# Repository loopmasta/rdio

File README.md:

# rdio

**rdio** turns your iPhone into a VHF/UHF radio. It connects to one or more ESP32-powered devices equipped with radio modules over Wi-Fi. Listen to transmissions, talk with push-to-talk, save your favourite channels and repeaters, and exchange APRS messages in a familiar chat-style interface.

**[Get the app on the App Store](https://apps.apple.com/de/app/rdio/id6831735571?l=en-GB)**

<table>
  <tr>
    <td align="center"></td>
    <td align="center"></td>
    <td align="center"></td>
    <td align="center"></td>
    <td align="center"></td>
  </tr>
  <tr>
    <td align="center">Main screen</td>
    <td align="center">Transmit</td>
    <td align="center">APRS chat</td>
    <td align="center">Channel editor</td>
    <td align="center">Settings</td>
  </tr>
</table>

## How it works

- The ESP32 opens its own Wi-Fi network (or joins one you configure). The phone connects to it and talks to the radio over a WebSocket. Radios on a shared network are found automatically (Bonjour), so one app can control several of them.
- Receive audio goes from the radio to the phone as 16 kHz mono PCM. Transmit audio goes the other way while you hold the push-to-talk button.
- The module is tuned, squelched and keyed by the ESP32 through its UART, PTT and power-down lines.
- Bluetooth is not used.

## Features

- **Receive and transmit** in the selected band (VHF 134–174 MHz or UHF 400–480 MHz).
- **Channel list** with simplex and duplex (repeater) entries, shift direction and offset, CTCSS transmit and receive tones, and a 1750 Hz tone burst. Reorder by dragging, swipe to edit or delete.
- **APRS** on 1200 baud AFSK: the app decodes received packets (positions, Mic-E, messages, status) on APRS channels, shows them as a chat with distance and a link to Maps, links call signs to QRZ.com. You can also send: type a message in the chat to a call sign or to CQ. Messages to a station are repeated until it acknowledges them, the app acknowledges messages addressed to you, and everything is sent only while the channel is clear. A periodic position beacon is available too.
- **Several radios:** each radio announces itself on the network as a Bonjour service (`_rdio._tcp`, with its name, module type and firmware version). The app lists the radios it finds in Settings → Radio and switches between them with one tap. Give every radio its own name (Settings → Radio Name), because the name is also its Wi-Fi and host name.
- **Phone microphone chain** with a compressor and a mic level setting, soft limiter on the radio side.
- **Native iOS design**: system controls, Light and Dark Mode, Dynamic Type, VoiceOver, haptics, no navigation bar.
- **Transmit safety**: the app only transmits inside the selected band, and the firmware releases the push-to-talk line when the connection drops, when no audio arrives, and after 120 seconds. Only one client can transmit.
- **Transmit power:** high (1 W) or low (0.5 W) with a switch in Settings → Radio. The radio remembers the choice; low power draws about half as much from the battery while transmitting.
- Firmware updates over Wi-Fi.

## Status

Working on a real radio: receive, transmit, channel handling, tones, tone burst, APRS decoding, and the APRS position beacon (tested over the air).

Not done yet: a scan function in the app.

The carrier board is built and works: receive, transmit, the transmit audio level and the power switch were tested on the air. The harmonic filters below are **designed but not built or measured yet**. They are simulated only; check them with a NanoVNA before relying on them.

## Hardware

Everything is KiCad 10 and is generated by scripts, so the boards can be rebuilt and changed in code.

### Carrier board

A 57.3 × 25.4 mm two-layer board for an ESP32 38-pin DevKit (NodeMCU-32S style) and a DRA818 / SA818 module. The DevKit's own pins are soldered into the board from below, the radio module sits on the top side, and an SMA jack on the end opposite the DevKit's USB port carries the antenna signal on a short track.

<table>
  <tr>
    <td align="center"></td>
    <td align="center"></td>
  </tr>
  <tr>
    <td align="center">Top: radio module, DevKit below, SMA jack</td>
    <td align="center">Bottom: audio and supply parts, DevKit pin rows</td>
  </tr>
</table>

| Function | ESP32 pin |
|---|---|
| Module UART (RX / TX) | GPIO16 / GPIO17 |
| Power down (high = on) | GPIO19 |
| PTT (low = transmit) | GPIO18 |
| Squelch in | GPIO32 |
| RX audio in (ADC) | GPIO34, biased to 1.75 V by GPIO26 |
| TX audio out | GPIO25 |
| High / low power | GPIO23 (the firmware pulls it low for 0.5 W and leaves it floating for 1 W; it never drives it high) |

- The module's supply pin is fed straight from the DevKit's 5 V pin, with a 47 µF and a 100 nF capacitor next to the module. The module's datasheet allows 3.3 to 4.5 V, so check the voltage on your DevKit's 5 V pin (many boards drop it through a diode from USB) before the first power-up.
- Pin numbers, the module name and the antenna end are printed on the top silkscreen inside the module outline, to help with placing it.
- Test status: built and working. The module's footprint and the DevKit's pin spacing were checked against real parts. The transmit network (22 k in series, 220 Ω and 220 nF to ground) divides the signal by about 100 and rolls it off from a few hundred hertz, so the firmware compensates with a higher transmit gain and a first-order treble boost (`firmware/idf/main/board.h`); the level and the frequency response were checked through a second radio.

### Harmonic filters (2 m and 70 cm)

Two small all-SMD low-pass filters (7th-order Chebyshev, 0.1 dB ripple, 50 Ω) that go between the board's SMA jack and the antenna and cut the radio module's harmonics. Details, simulation and parts notes: [hardware/filter/README.md](hardware/filter/README.md).

<table>
  <tr>
    <td align="center"></td>
    <td align="center"></td>
  </tr>
  <tr>
    <td align="center">2 m, 144–146 MHz</td>
    <td align="center">70 cm, 430–440 MHz</td>
  </tr>
</table>

| | 2 m | 70 cm |
|---|---|---|
| Passband | 144–146 MHz | 430–440 MHz |
| Insertion loss (simulated) | 0.56 dB | 0.50 dB |
| 2nd harmonic (simulated) | 52 dB down | 63 dB down |
| Board size | 38.0 × 12.4 mm | 34.4 × 12.4 mm |

### Ordering the boards

Gerber, drill, bill of materials and placement files for JLCPCB are in [hardware/jlcpcb/](hardware/jlcpcb/): `radio/` for the carrier board and `filters/vhf`, `filters/uhf` for the filters. Check the LCSC part numbers in the bills of materials against JLCPCB's parts library before you order. The SMA connectors, the DevKit headers and the radio module are soldered by hand.

## Legal

Transmitting needs an amateur radio licence and must follow the rules that apply to you. The app limits the transmit frequency to the selected band, but you are responsible for staying within your licence and the local regulations.

**Privacy:** the app has no accounts, analytics or tracking. See the [privacy policy](https://loopmasta.github.io/rdio/privacy/).

## Repository contents

This repository lets a small group of testers order the hardware, build it, flash the firmware and install the app, with no software knowledge or development tools. It holds the hardware design (`hardware/`), the screenshots (`docs/`) and this description.

The software is not included and does not need to be built:

- **iOS app:** [download rdio from the App Store](https://apps.apple.com/de/app/rdio/id6831735571?l=en-GB).
- **Firmware:** installed from your browser with the [web flasher](https://loopmasta.github.io/rdio/flash/). Connect the ESP32 over USB, open the page in Chrome or Edge on a computer and press install.

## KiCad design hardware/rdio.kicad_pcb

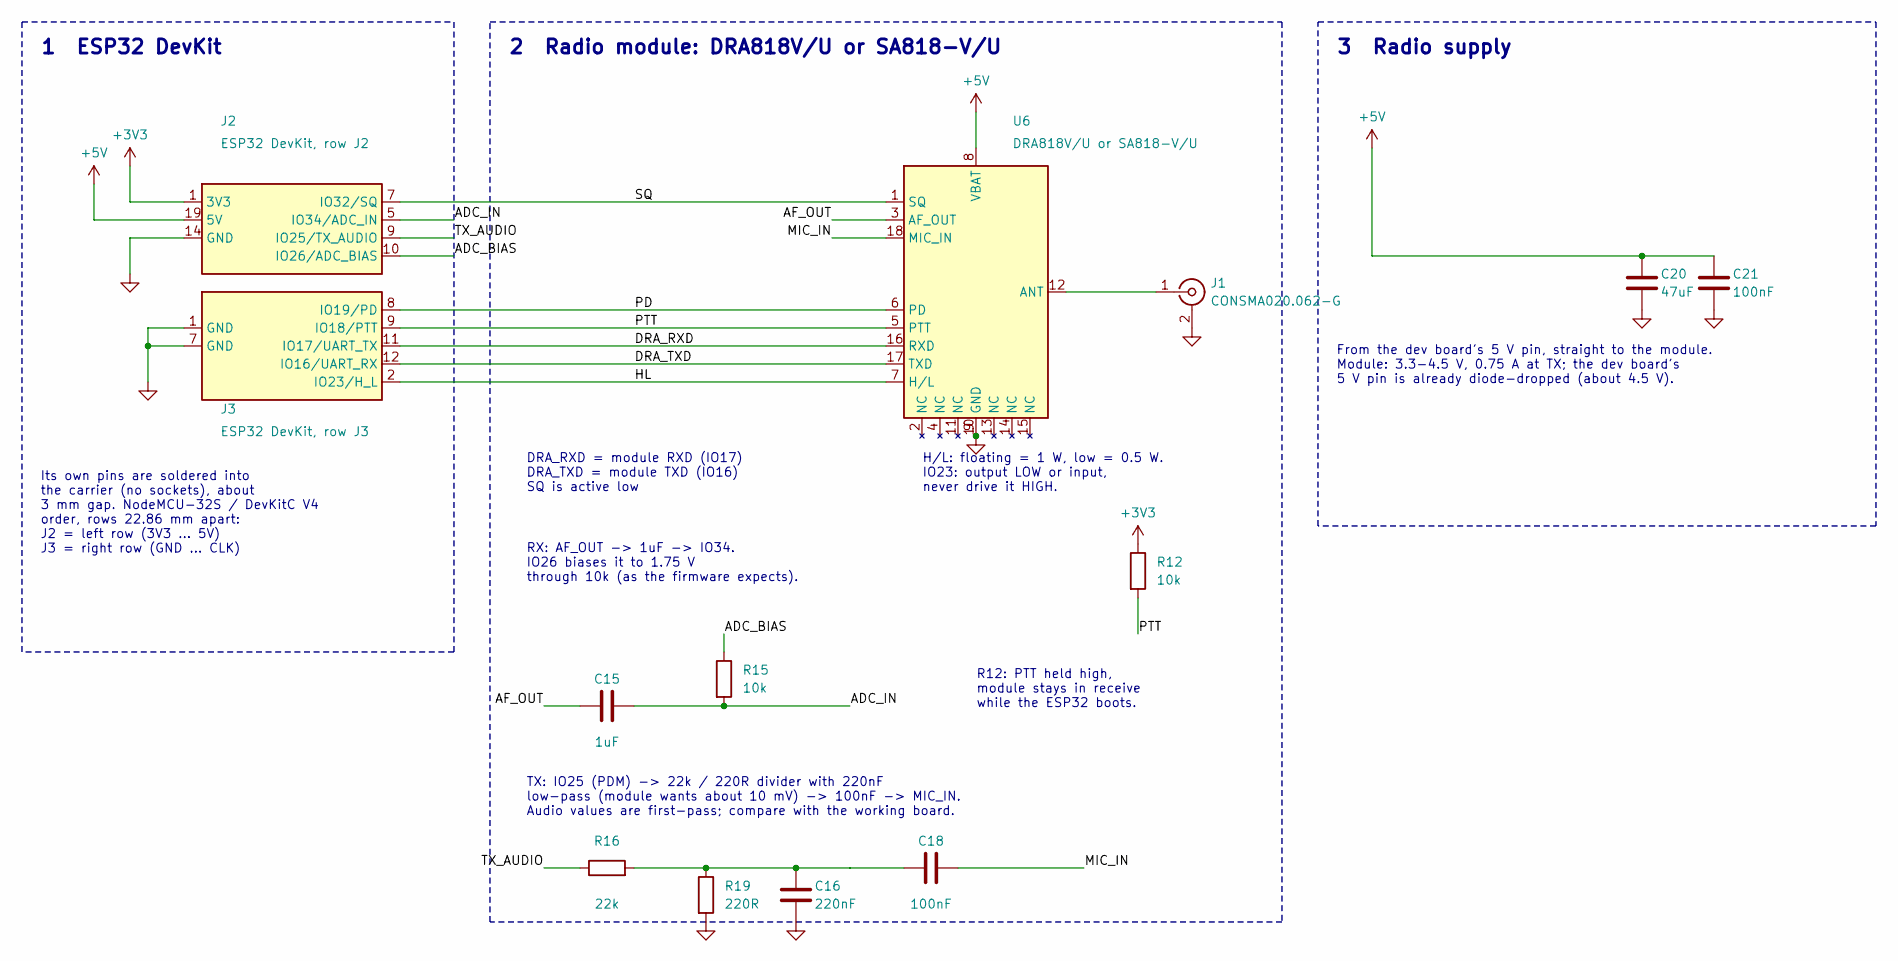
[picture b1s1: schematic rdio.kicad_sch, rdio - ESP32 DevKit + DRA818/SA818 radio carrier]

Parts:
C15: 1uF; C_0603_1608Metric
C16: 220nF; C_0603_1608Metric
C18, C21: 100nF; C_0603_1608Metric
C20: 47uF; C_1206_3216Metric
J1: CONSMA020.062-G; CONSMA020_062_G
J2: ESP32 DevKit, row J2; PinHoles_1x19_P2.54mm
J3: ESP32 DevKit, row J3; PinHoles_1x19_P2.54mm
R12, R15: 10k; R_0603_1608Metric
R16: 22k; R_0603_1608Metric
R19: 220R; R_0603_1608Metric
U6: DRA818V/U or SA818-V/U; DRA818_SA818

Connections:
+3V3: J2.1 (3V3), R12.1
+5V: C20.1, C21.1, J2.19 (5V), U6.8 (VBAT)
/ADC_BIAS: J2.10 (IO26/ADC_BIAS), R15.1
/ADC_IN: C15.2, J2.5 (IO34/ADC_IN), R15.2
/AF_OUT: C15.1, U6.3 (AF_OUT)
/DRA_RXD: J3.11 (IO17/UART_TX), U6.16 (RXD)
/DRA_TXD: J3.12 (IO16/UART_RX), U6.17 (TXD)
/HL: J3.2 (IO23/H_L), U6.7 (H/L)
/MIC_IN: C18.2, U6.18 (MIC_IN)
/PD: J3.8 (IO19/PD), U6.6 (PD)
/PTT: J3.9 (IO18/PTT), R12.2, U6.5 (PTT)
/SQ: J2.7 (IO32/SQ), U6.1 (SQ)
/TX_AUDIO: J2.9 (IO25/TX_AUDIO), R16.1
GND: C16.2, C20.2, C21.2, J1.2 (Ext), J2.14 (GND), J3.1 (GND), J3.7 (GND), R19.2, U6.9 (GND), U6.10 (GND)
unnamed: C16.1, C18.1, R16.2, R19.1
unnamed: J1.1 (In), U6.12 (ANT)

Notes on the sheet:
1 ESP32 DevKit
Its own pins are soldered into the carrier (no sockets), about 3 mm gap. NodeMCU-32S / DevKitC V4 order, rows 22.86 mm apart: J2 = left row (3V3 ... 5V) J3 = right row (GND ... CLK)
2 Radio module: DRA818V/U or SA818-V/U
DRA_RXD = module RXD (IO17) DRA_TXD = module TXD (IO16) SQ is active low
H/L: floating = 1 W, low = 0.5 W. IO23: output LOW or input, never drive it HIGH.
R12: PTT held high, module stays in receive while the ESP32 boots.
RX: AF_OUT -> 1uF -> IO34. IO26 biases it to 1.75 V through 10k (as the firmware expects).
TX: IO25 (PDM) -> 22k / 220R divider with 220nF low-pass (module wants about 10 mV) -> 100nF -> MIC_IN. Audio values are first-pass; compare with the working board.
3 Radio supply
From the dev board's 5 V pin, straight to the module. Module: 3.3-4.5 V, 0.75 A at TX; the dev board's 5 V pin is already diode-dropped (about 4.5 V).

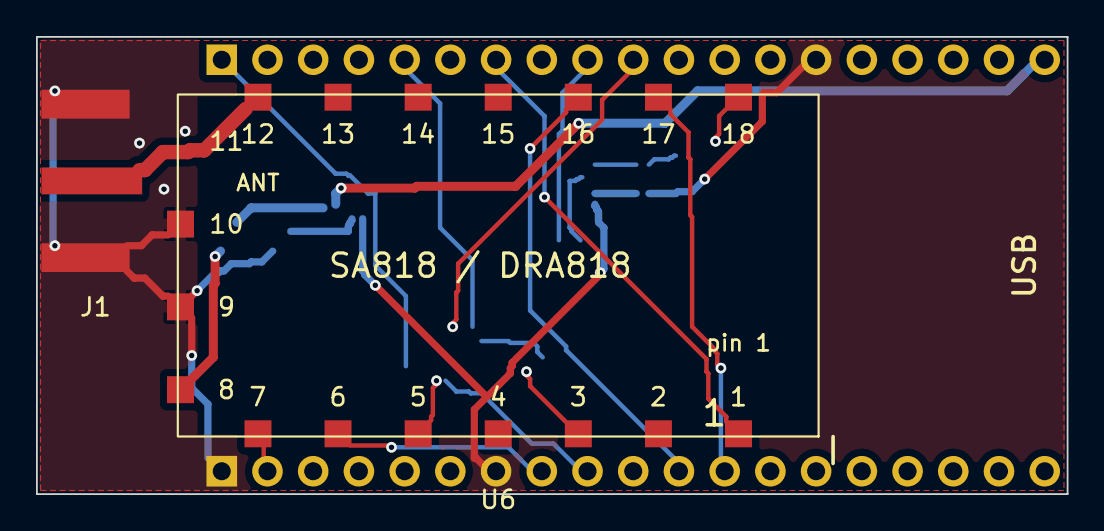
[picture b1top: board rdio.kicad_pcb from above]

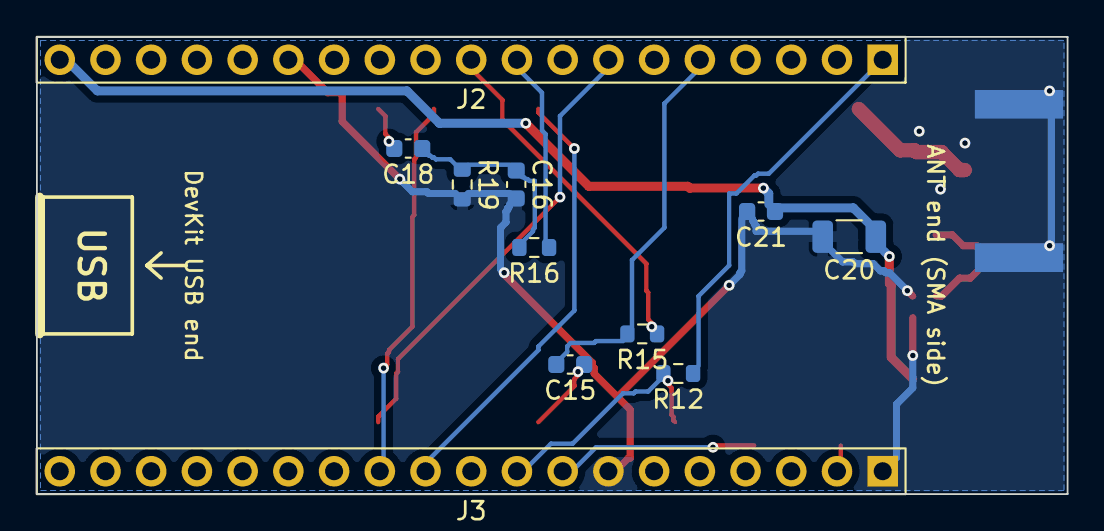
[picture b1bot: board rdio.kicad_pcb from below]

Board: 2 copper layers, 57.3 x 25.4 mm, 14 parts (11 on the bottom side), 16 nets.

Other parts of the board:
DK1: ESP32_DevKit_38pin

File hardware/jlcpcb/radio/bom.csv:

Comment,Designator,Footprint,LCSC Part #
1uF,C15,C_0603_1608Metric,C15849
220nF,C16,C_0603_1608Metric,C23630
100nF,"C18,C21",C_0603_1608Metric,C14663
47uF,C20,C_1206_3216Metric,C96123
10k,"R12,R15",R_0603_1608Metric,C25804
22k,R16,R_0603_1608Metric,C31850
220R,R19,R_0603_1608Metric,C22962

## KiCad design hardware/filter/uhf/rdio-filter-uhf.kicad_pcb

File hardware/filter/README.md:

# Harmonic filters for the radio (2 m and 70 cm)

Two small all-SMD low-pass filters. Each goes between the carrier board's SMA connector and the antenna and cuts the
radio module's harmonics (the second harmonic is the one that matters). 7th-order Chebyshev (0.1 dB ripple), 50 ohm,
shunt-C first: C1 - L1 - C2 - L2 - C3 - L3 - C4. SMA in on one end, SMA out on the other, solid ground on both layers.

| | 2 m (`vhf/`) | 70 cm (`uhf/`) |
|---|---|---|
| Passband | 144-146 MHz | 430-440 MHz |
| Filter edge (0.1 dB) | 155 MHz | 460 MHz |
| C1 = C4 | 22 pF | 8.2 pF |
| L1 = L3 | 68 nH | 22 nH |
| C2 = C3 | 39 pF | 13 pF |
| L2 | 82 nH | 27 nH |
| Capacitors | C0G/NP0, 0402, 50 V | C0G/NP0, 0402, 50 V |
| Inductors | high-Q chip, 0603 | high-Q chip, 0402 |
| Board size | 38.0 x 12.4 mm | 34.4 x 12.4 mm |
| Insertion loss (simulated) | 0.56 dB | 0.50 dB |
| Return loss in band (simulated) | 36 dB | 27 dB |
| 2nd harmonic (simulated) | 52 dB down | 63 dB down |
| Worst case, 5 % parts, 500 runs | 0.77 dB loss, 50 dB at 2nd harmonic | 0.75 dB loss, 60 dB at 2nd harmonic |

Simulated response of the two filters:

<table>
  <tr>
    <td align="center"></td>
    <td align="center"></td>
  </tr>
  <tr>
    <td align="center">2 m, 144–146 MHz</td>
    <td align="center">70 cm, 430–440 MHz</td>
  </tr>
</table>

## What is simulated and what is not

The simulation (`../tools/filter_sim.py`) includes inductor Q (70 / 90), the inductors' winding capacitance, capacitor ESL and
ESR, and component tolerance. It does not include the board: pad and via parasitics, coupling between neighbouring parts,
and the SMA transitions. The board is a straight 50-ohm line with the shunt capacitors going to ground vias right at their
pads, but it has not been measured. Expect a few percent shift in the filter edge. Measure S21 and S11 with a NanoVNA
before relying on it, and trim a capacitor by one step if the passband edge is off. The very high simulated attenuation at
the 3rd and 5th harmonics (85 dB and more) is not realistic on a real board; coupling limits it to roughly 60-70 dB.
This is a design aid, not a compliance measurement.

## Parts notes

- Check that the inductor values exist in the series you pick (for example Coilcraft 0603HP or Murata LQW18 for 68/82 nH,
  Coilcraft 0402HP or Murata LQW15 for 22/27 nH) and that the Q is at least 50 at the band.
- 0402 parts are small to hand-solder. The 0603 inductors on the 2 m board are easier.
- The shunt capacitors see about 7 V peak at 1 W; 50 V C0G is plenty.
- Connectors: `J1` (marked RADIO) is an SMA **male plug**, the threaded kind with a coupling nut, so it screws straight onto
  the carrier's SMA jack with no adapter. `J2` (marked ANTENNA) is the **TE/Linx CONSMA020.062-G** SMA jack (female, edge mount,
  for 0.062 in = 1.57 mm boards, 50 ohm, to 18 GHz). Its footprint (`rdio-filter.pretty/CONSMA020_062_G`) is built from the
  Linx drawing's "recommended footprint": RF pad 1.5 x 5.6 mm, four ground pads 1.6 x 4.9 mm at 4.26 mm (two on each layer),
  recessed 0.25 mm from the board edge to keep the copper-to-edge clearance. The 6.5 mm "mounting hole" in that drawing is a
  panel cut-out, not a PCB hole. The 3D bodies of both connectors are simple placeholders.
  The plug (`SMA_Plug_EdgeMount`) copies the pad pattern of the Amphenol edge-launch jack; use a plug whose datasheet matches it,
  or tell me the part and I will build its footprint from the datasheet.
  Order the boards 1.6 mm thick (the connector is specified for 1.57 mm).
  Open the filters as their own projects: `vhf/rdio-filter-vhf.kicad_pro` and `uhf/rdio-filter-uhf.kicad_pro`.
- The filter loses 0.5-0.8 dB (about 11-16 % of the power). That is the price of the harmonic rejection.

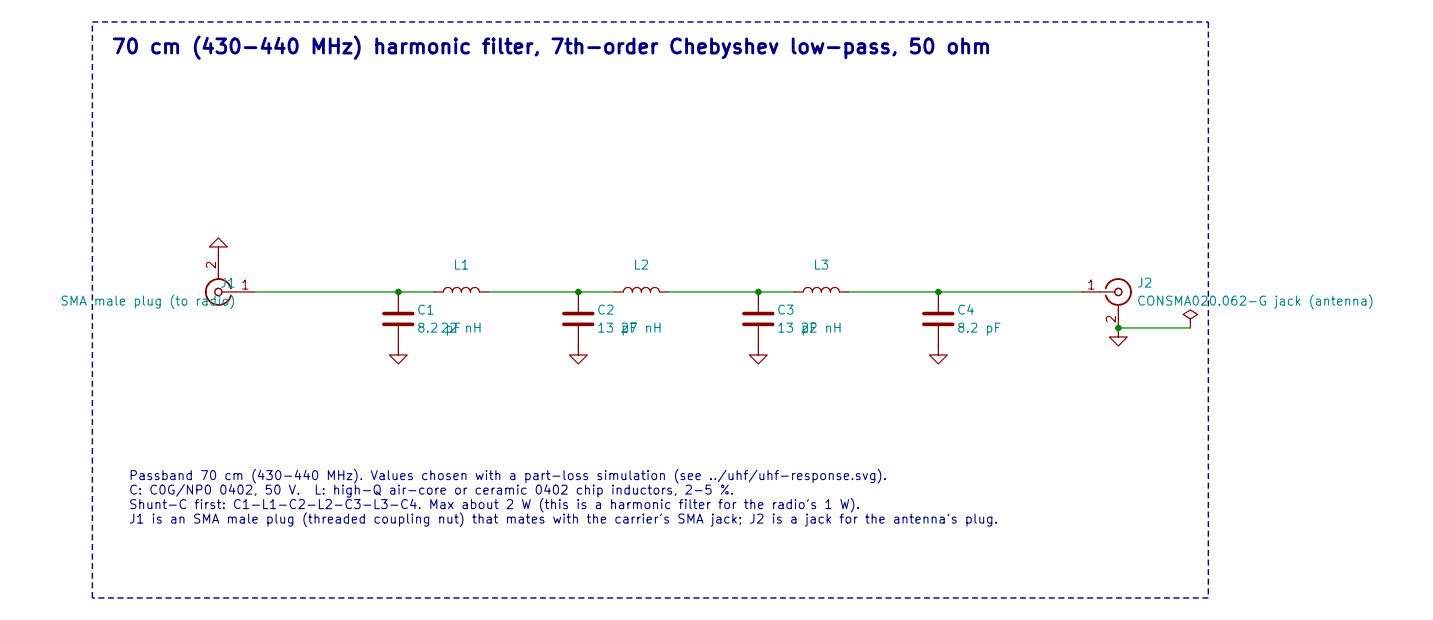
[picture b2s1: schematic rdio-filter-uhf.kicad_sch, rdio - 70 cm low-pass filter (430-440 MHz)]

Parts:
C1, C4: 8.2 pF; C_0402_1005Metric
C2, C3: 13 pF; C_0402_1005Metric
J1: SMA male plug (to radio); SMA_Plug_EdgeMount
J2: CONSMA020.062-G jack (antenna); CONSMA020_062_G
L1, L3: 22 nH; L_0402_1005Metric
L2: 27 nH; L_0402_1005Metric

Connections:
GND: C1.2, C2.2, C3.2, C4.2, J1.2 (Ext), J2.2 (Ext)
unnamed: C2.1, L1.2, L2.1
unnamed: C3.1, L2.2, L3.1
unnamed: C1.1, J1.1 (In), L1.1
unnamed: C4.1, J2.1 (In), L3.2

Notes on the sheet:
70 cm (430-440 MHz) harmonic filter, 7th-order Chebyshev low-pass, 50 ohm
Passband 70 cm (430-440 MHz). Values chosen with a part-loss simulation (see ../uhf/uhf-response.svg). C: C0G/NP0 0402, 50 V. L: high-Q air-core or ceramic 0402 chip inductors, 2-5 %. Shunt-C first: C1-L1-C2-L2-C3-L3-C4. Max about 2 W (this is a harmonic filter for the radio's 1 W). J1 is an SMA ma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

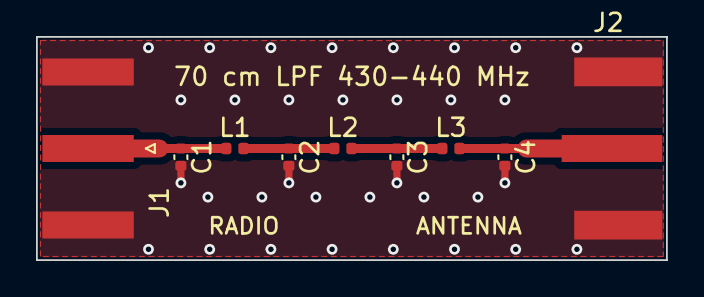
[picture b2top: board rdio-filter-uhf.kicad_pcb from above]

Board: 2 copper layers, 35.0 x 12.4 mm, 9 parts (0 on the bottom side), 5 nets.

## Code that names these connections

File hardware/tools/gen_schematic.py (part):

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			(name {q(name)} (effects (font (size 1.27 1.27))))
			(number {q(num)} (effects (font (size 1.27 1.27)))))'''
    pins = [
        pin("output", -12.7, 12.7, 0, "SQ", "1"), pin("output", -12.7, 10.16, 0, "AF_OUT", "3"),
        pin("input", -12.7, 7.62, 0, "MIC_IN", "18"), pin("input", -12.7, -2.54, 0, "PD", "6"),
        pin("input", -12.7, -5.08, 0, "PTT", "5"), pin("input", -12.7, -7.62, 0, "RXD", "16"),
        pin("output", -12.7, -10.16, 0, "TXD", "17"), pin("input", -12.7, -12.7, 0, "H/L", "7"),
        pin("passive", 12.7, 0, 180, "ANT", "12"),
        pin("power_in", 0, 20.32, 270, "VBAT", "8"),
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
